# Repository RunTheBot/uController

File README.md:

# µController

µController (micro controller) a tiny battery powered game controller design for one game...unrailed

This way, you can ruin friendships with unrailed anywhere, anytime.

# Features
- Hall effect PS4 style joysticks
- 2 Cherry MX keys for use and dash inputs
- Neopixel RGB LED under Cherry MX keys
- 5v boost converter for neopixel running off 3.7v battery
- USB-C charging port
- Battery charging
- Battery voltage sensor
- Battery level indicator
- Ultra low power mode
  - Deep sleep mode with wake on button press
  - Disables boost converter and neopixel
  - Disables Wireless connection
- Ultra Small: 79mm x 33mm
- Wireless

# BOM

| Name                       | Quantity | Single Unit Price | Total Price | URL/LCSC                                                                      | Vendor (LCSC unless otheriwse indicated) |                  |
|----------------------------|----------|-------------------|-------------|-------------------------------------------------------------------------------|------------------------------------------|------------------|
| Electronics                |          |                   |             |                                                                               |                                          |                  |
| C5 0603 0.1uF              | 3        |                   | $0.45       | C49678                                                                        |                                          |                  |
| C3 0603 10uF               | 1        |                   | $0.13       | C19702                                                                        |                                          |                  |
| C4 0603 22uF               | 1        |                   | $0.18       | C59461                                                                        |                                          |                  |
| LED 0603                   | 1        |                   | $0.32       | C965799                                                                       |                                          |                  |
| SK6812MINI                 | 2        |                   | $0.37       | C5149201                                                                      |                                          |                  |
| schottky diode             | 2        |                   |             | C85098                                                                        |                                          | With NotAHackPad |
| BSS138 (Level Shifter)     | 1        |                   |             | C82045                                                                        |                                          | With NotAHackPad |
| USB_C_Receptacle           | 1        |                   | $0.38       | C2988369                                                                      |                                          |                  |
| 2.2µH/±20%/1.5A Inductor   | 1        |                   | $0.67       | C171762                                                                       |                                          |                  |
| 0603 R5.1kΩ                | 2        |                   | $0.09       | C2907044                                                                      |                                          |                  |
| 0603 1.8M                  | 1        |                   | $0.08       | C2930026                                                                      |                                          |                  |
| 0603 200k                  | 1        |                   | $0.12       | C105574                                                                       |                                          |                  |
| 0603 120Ω                  | 1        |                   | $0.13       | C114640                                                                       |                                          |                  |
| 0603 10K                   | 3        |                   |             | C98220                                                                        | With NotAHackPad                         |                  |
| 0603 15kΩ                  | 1        |                   | $0.09       | C2906995                                                                      |                                          |                  |
| 0603 100kΩ                 | 2        |                   | $0.10       | C14675                                                                        |                                          |                  |
| SW_Push_SPST_NO_Alps_SKRK  | 2        |                   | $0.63       | C115357                                                                       |                                          |                  |
| NanoS3                     | 1        |                   | $19.00      | https://unexpectedmaker.com/shop.html#!/NanoS3/p/577095557/category=154217256 | UM                                       |                  |
| TPS61200DRC                | 1        |                   | $1.63       | C140320                                                                       |                                          |                  |
| PS4 Joystick Hall Effect   | 1        |                   | $4.59       | https://www.aliexpress.com/item/1005008600410715.html                         |                                          |                  |
| BT2.0 U CablePigtail (180) | 1        |                   | $8.20       | https://www.aliexpress.com/item/1005008719531779.html                         |                                          |                  |
| Battery                    | 1        |                   | $25.79      | https://www.aliexpress.com/item/1005008702820863.html                         |                                          |                  |
| LCSC Shipping/handling     |          |                   | $15.14      |                                                                               |                                          |                  |
| UM Shipping                |          |                   | $12.95      |                                                                               |                                          |                  |
| Keys                       |          |                   |             |                                                                               |                                          |                  |
| Outemu Silent Grays        | 1        | $22.38            | $22.38      | https://www.aliexpress.com/item/1005007052759423.html                         |                                          |                  |
| Key Caps - Printed         |          |                   | $0.00       |                                                                               |                                          |                  |
| JLC                        |          |                   |             |                                                                               |                                          |                  |
| PCB with stencil           | 1        | $9.00             | $9.00       |                                                                               |                                          |                  |
| Shipping                   | 1        | $16.88            | $16.88      |                                                                               |                                          |                  |
|                            |          |                   |             |                                                                               |                                          |                  |
|                            |          |                   | $60.96      | CAD                                                                           |                                          |                  |
|                            |          |                   | $59.34      | USD                                                                           |                                          |                  |
|                            |          |                   | $103.89     | Total - USD                                                                   |                                          |                  |

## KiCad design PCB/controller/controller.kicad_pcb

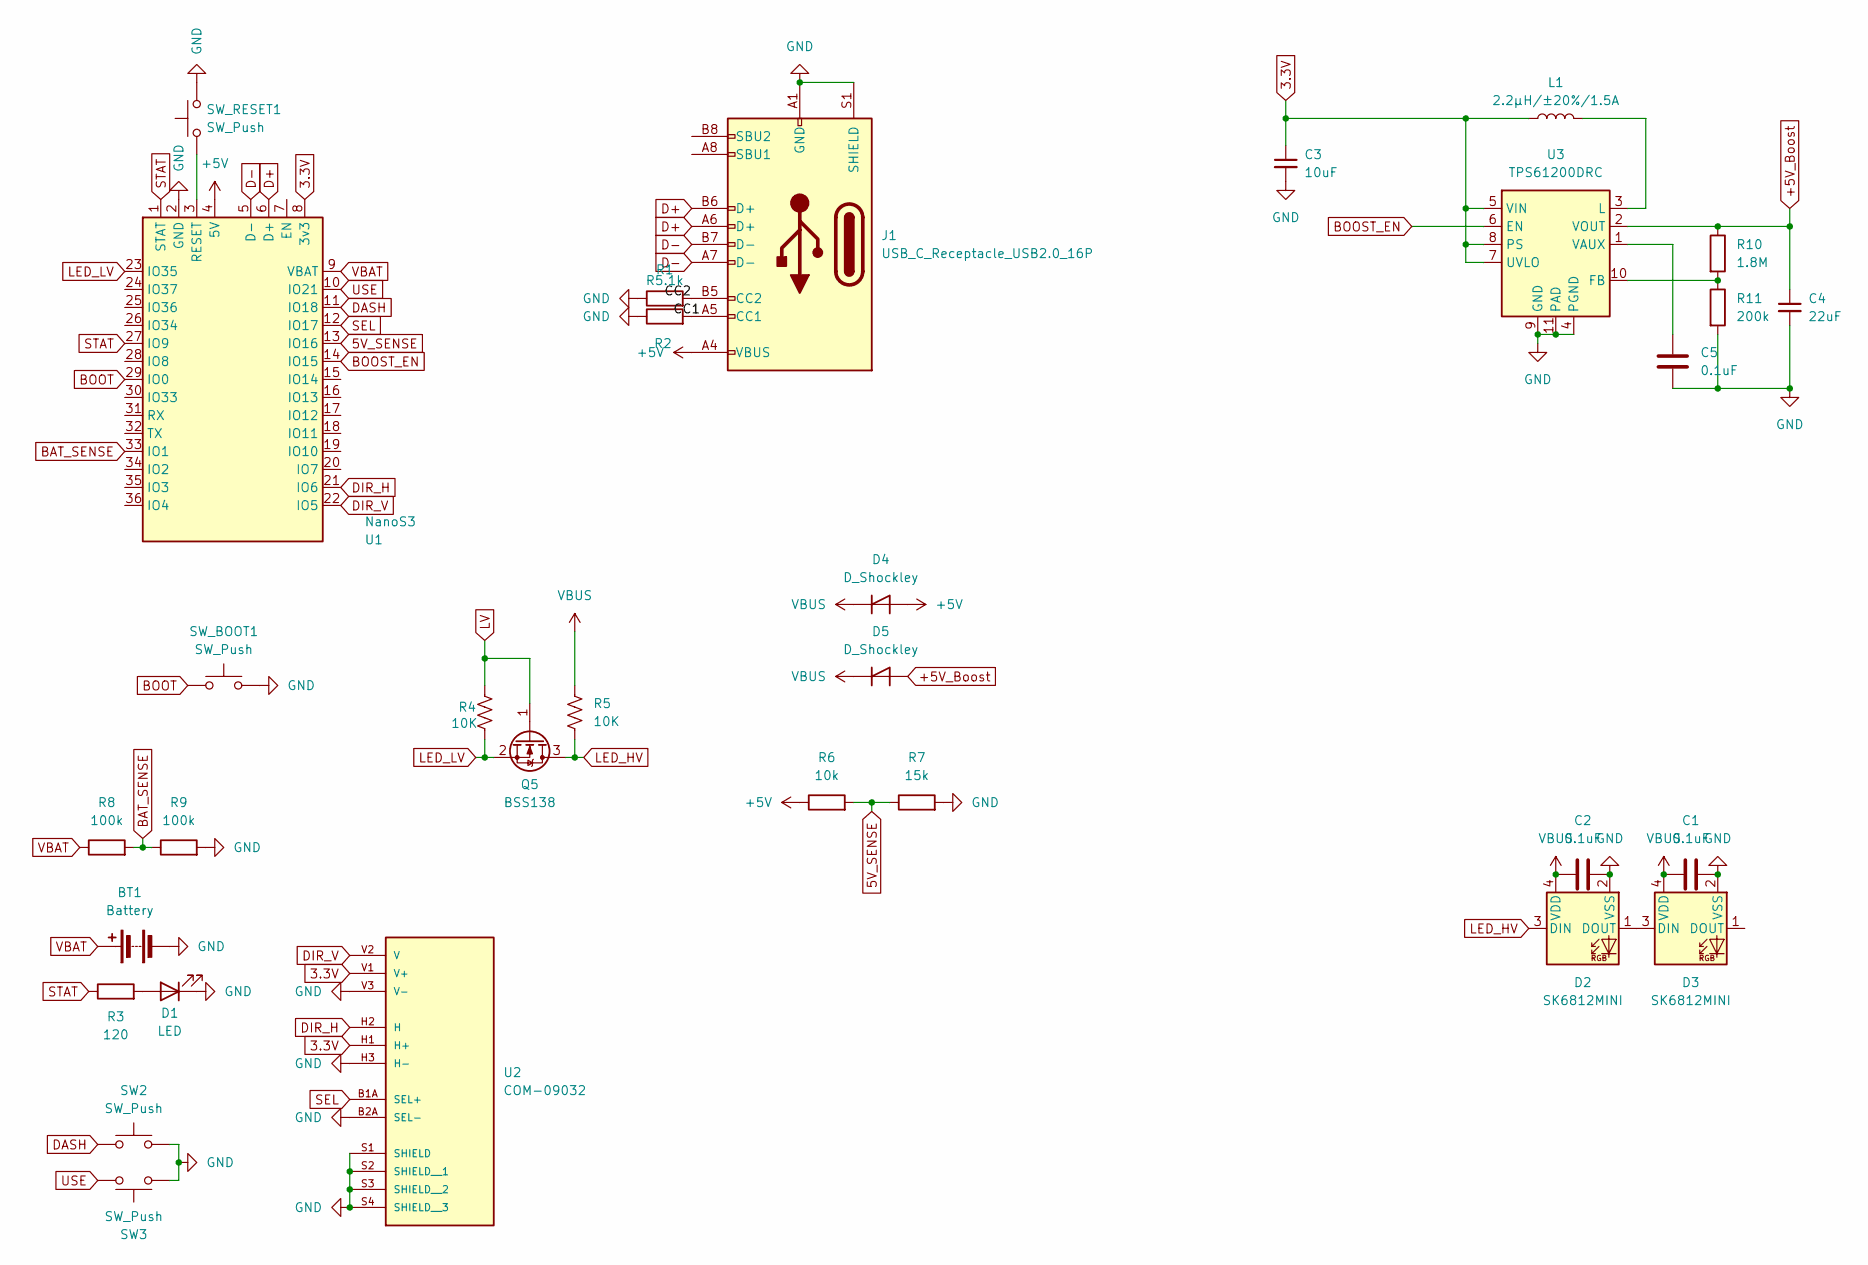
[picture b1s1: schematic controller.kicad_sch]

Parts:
BT1: Battery; JST_XH_S2B-XH-A_1x02_P2.50mm_Horizontal
C1, C2: 0.1uF; C_0805_2012Metric_Pad1.18x1.45mm_HandSolder
C3: 10uF; C_0603_1608Metric_Pad1.08x0.95mm_HandSolder
C4: 22uF; C_0603_1608Metric_Pad1.08x0.95mm_HandSolder
C5: 0.1uF; C_0603_1608Metric_Pad1.08x0.95mm_HandSolder
D1: LED; LED_0603_1608Metric_Pad1.05x0.95mm_HandSolder
D2, D3: SK6812MINI; SK6812MINI-E
D4, D5: D_Shockley; D_SMA-SMB_Universal_Handsoldering
J1: USB_C_Receptacle_USB2.0_16P; USB_C_Receptacle_G-Switch_GT-USB-7010ASV
L1: 2.2µH/±20%/1.5A; L_1008_2520Metric_Pad1.43x2.20mm_HandSolder
Q5: BSS138; SOT-23
R1, R2: R5.1k; R_0603_1608Metric_Pad0.98x0.95mm_HandSolder
R3: 120; C_0603_1608Metric_Pad1.08x0.95mm_HandSolder
R4, R5: 10K; R_0603_1608Metric_Pad0.98x0.95mm_HandSolder
R6: 10k; R_0603_1608Metric_Pad0.98x0.95mm_HandSolder
R7: 15k; R_0603_1608Metric_Pad0.98x0.95mm_HandSolder
R8, R9: 100k; R_0603_1608Metric_Pad0.98x0.95mm_HandSolder
R10: 1.8M; R_0603_1608Metric_Pad0.98x0.95mm_HandSolder
R11: 200k; R_0603_1608Metric_Pad0.98x0.95mm_HandSolder
SW2, SW3: SW_Push; SW_Cherry_MX_PCB_1.00u
SW_BOOT1: SW_Push; SW_Push_SPST_NO_Alps_SKRK
SW_RESET1: SW_Push; SW_Push_SPST_NO_Alps_SKRK
U1: NanoS3; NanoS3_HandSolder
U2: COM-09032; PS4_joystick; PARTREV N/A
U3: TPS61200DRC; Texas_S-PVSON-N10_ThermalVias

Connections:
3.3V: C3.1, L1.1, U1.8 (3v3), U2.H1 (H+), U2.V1 (V+), U3.5 (VIN), U3.7 (UVLO), U3.8 (PS)
5V_SENSE: R6.2, R7.1, U1.13 (IO16)
+5V: D4.2 (A), J1.A4 (VBUS), J1.A9 (VBUS), J1.B4 (VBUS), J1.B9 (VBUS), R6.1, U1.4 (5V)
+5V_Boost: C4.1, D5.2 (A), R10.1, U3.2 (VOUT)
/CC2: J1.B5 (CC2), R1.2
BAT_SENSE: R8.2, R9.1, U1.33 (IO1)
BOOST_EN: U1.14 (IO15), U3.6 (EN)
BOOT: SW_BOOT1.1, U1.29 (IO0)
D+: J1.A6 (D+), J1.B6 (D+), U1.6 (D+)
D-: J1.A7 (D-), J1.B7 (D-), U1.5 (D-)
DASH: SW2.1, U1.11 (IO18)
DIR_H: U1.21 (IO6), U2.H2 (H)
DIR_V: U1.22 (IO5), U2.V2 (V)
GND: BT1.2 (-), C1.2, C2.2, C3.2, C4.2, C5.1, D1.1 (K), D2.2 (VSS), D3.2 (VSS), J1.A1 (GND), J1.A12 (GND), J1.B1 (GND), J1.B12 (GND), J1.S1 (SHIELD), R1.1, R2.1, R7.2, R9.2, R11.2, SW2.2, SW3.1, SW_BOOT1.2, SW_RESET1.2, U1.2 (GND), U2.B2A (SEL-), U2.H3 (H-), U2.S1 (SHIELD), U2.S2 (SHIELD__1), U2.S3 (SHIELD__2), U2.S4 (SHIELD__3), U2.V3 (V-), U3.4 (PGND), U3.9 (GND), U3.11 (PAD)
LED_HV: D2.3 (DIN), Q5.3 (D), R5.2
LED_LV: Q5.2 (S), R4.2, U1.23 (IO35)
LV: Q5.1 (G), R4.1
unnamed: D1.2 (A), R3.2
unnamed: D2.1 (DOUT), D3.3 (DIN)
unnamed: J1.A5 (CC1), R2.2
unnamed: SW_RESET1.1, U1.3 (RESET)
unnamed: R10.2, R11.1, U3.10 (FB)
unnamed: L1.2, U3.3 (L)
unnamed: C5.2, U3.1 (VAUX)
SEL: U1.12 (IO17), U2.B1A (SEL+)
STAT: R3.1, U1.1 (STAT), U1.27 (IO9)
USE: SW3.2, U1.10 (IO21)
VBAT: BT1.1 (+), R8.1, U1.9 (VBAT)
VBUS: C1.1, C2.1, D2.4 (VDD), D3.4 (VDD), D4.1 (K), D5.1 (K), R5.1

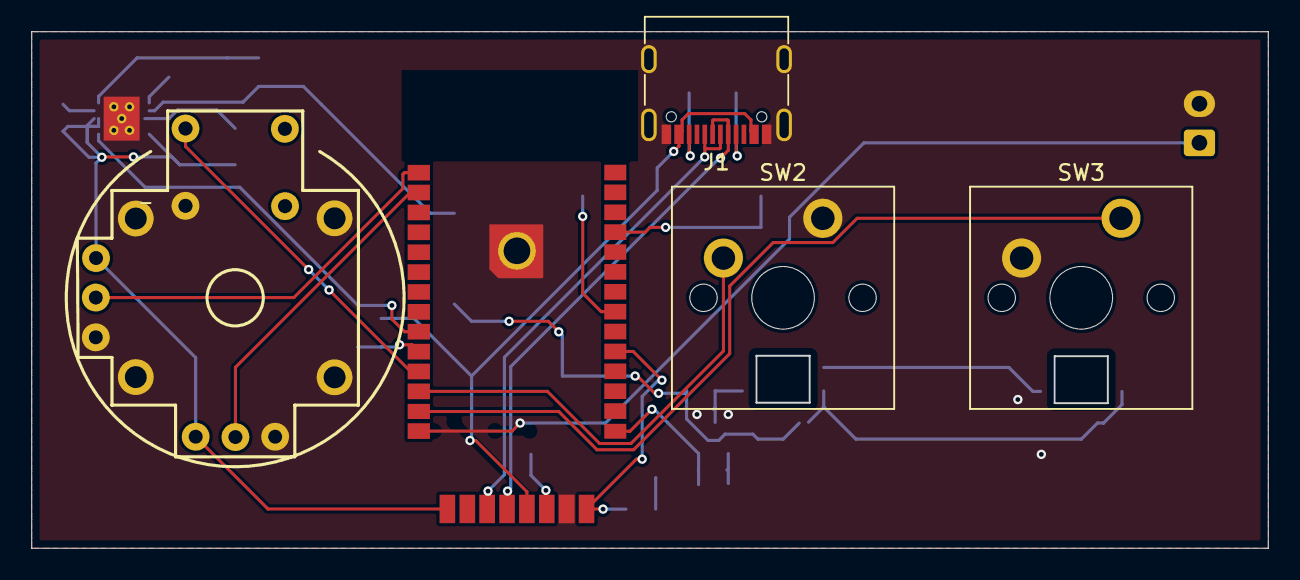
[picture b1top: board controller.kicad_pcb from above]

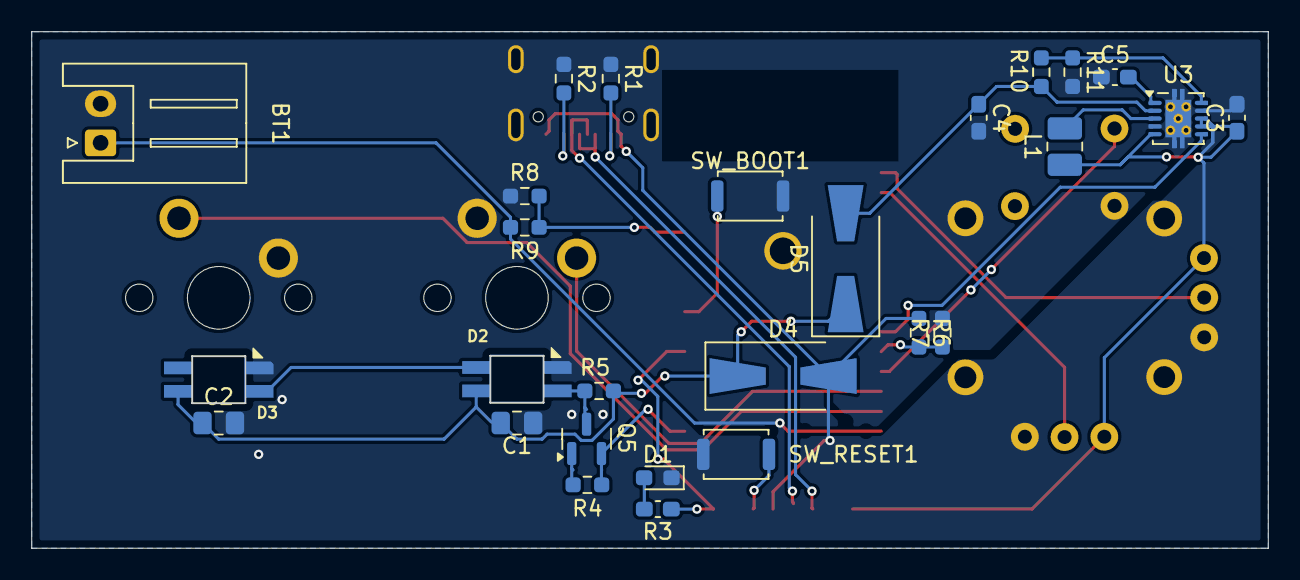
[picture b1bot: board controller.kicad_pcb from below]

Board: 2 copper layers, 78.9 x 32.9 mm, 32 parts (27 on the bottom side), 29 nets.

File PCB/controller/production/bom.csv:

Designator,Footprint,Quantity,Value,LCSC Part #
BT1,JST_XH_S2B-XH-A_1x02_P2.50mm_Horizontal,1,Battery,C493111
"C1, C2, C5",0805,3,0.1uF,C49678
C3,0603,1,10uF,C19702
C4,0603,1,22uF,C59461
D1,0603,1,LED,C965799
"D2, D3",SK6812MINI-E,2,SK6812MINI,C5149201
"D4, D5",D_SMA-SMB_Universal_Handsoldering,2,D_Shockley,C85098
J1,USB_C_Receptacle_XKB_U262-16XN-4BVC11,1,USB_C_Receptacle_USB2.0_16P,
L1,1008,1,2.2µH/±20%/1.5A,C2988369
Q5,SOT-23,1,BSS138,C171762
"R1, R2",0603,2,R5.1k,C2907044
R10,0603,1,1.8M,C2930026
R11,0603,1,200k,C105574
R3,0603,1,120,C114640
"R4, R5, R6",0603,3,10K,C98220
R7,0603,1,15k,C2906995
"R8, R9",0603,2,100k,C14675
"SW2, SW3",SW_Cherry_MX_PCB_1.00u,2,SW_Push,
"SW_BOOT1, SW_RESET1",SW_Push_SPST_NO_Alps_SKRK,2,SW_Push,C115357
U1,NanoS3_HandSolder,1,NanoS3,
U2,PS4_joystick,1,COM-09032,
U3,Texas_S-PVSON-N10_ThermalVias,1,TPS61200DRC,C140320

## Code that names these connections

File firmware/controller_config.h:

/*
 * ESP32-S3 Unrailed Controller Configuration
 * Hardware: NanoS3/Tiny Pico Nano
 */

#ifndef CONTROLLER_CONFIG_H
#define CONTROLLER_CONFIG_H

// Hardware version
#define HARDWARE_VERSION "NanoS3/Tiny Pico Nano"
#define FIRMWARE_VERSION "1.0.0"

// Pin definitions for ESP32-S3
#define LED_LV_PIN      35  // Status LED
#define BAT_STAT_PIN    9   // Battery Status Input
#define BAT_SENSE_PIN   1   // Battery Voltage ADC (100k/100k divider)
#define USE_PIN         21  // Button A (USE)
#define DASH_PIN        18  // Button B (DASH)
#define SEL_PIN         17  // Select Button
#define USB_5V_SENSE    16  // USB 5V Detection
#define BOOST_EN_PIN    15  // 5V Boost Enable
#define DIR_H_PIN       6   // Joystick Horizontal (X-axis)
#define DIR_V_PIN       5   // Joystick Vertical (Y-axis)

// Controller settings
#define CONTROLLER_NAME "Unrailed Controller"
#define MANUFACTURER    "ESP32"

// Joystick configuration
#define JOYSTICK_DEADZONE     100   // ADC units
#define JOYSTICK_CENTER       2048  // 12-bit ADC center
#define JOYSTICK_MAX_RANGE    2048  // Maximum deviation from center

// Battery configuration
#define BATTERY_CHECK_INTERVAL 5000  // milliseconds
#define BATTERY_MIN_VOLTAGE    3.0   // Volts
#define BATTERY_MAX_VOLTAGE    4.2   // Volts (fully charged Li-Po)
#define VOLTAGE_DIVIDER_RATIO  2.0   // 100k/100k = 2:1 ratio

// LED patterns
#define LED_BLINK_INTERVAL    500   // milliseconds (when not connected)
#define LED_STARTUP_BLINKS    3     // Number of blinks on startup

// Deep sleep configuration
#define SLEEP_TIMEOUT_MS         300000  // 5 minutes of inactivity before sleep
#define LOW_BATTERY_SLEEP_MS     30000   // 30 seconds between wake cycles when low battery
#define ACTIVITY_THRESHOLD       50      // Joystick movement threshold to detect activity
#define LOW_BATTERY_THRESHOLD    15      // Battery percentage threshold for extended sleep

// Wake up sources - Require ALL 3 buttons pressed simultaneously
#define WAKE_BUTTON_BITMASK      0x2A0000  // USE (GPIO21), DASH (GPIO18), and SEL (GPIO17) buttons
// Bitmask calculation: (1ULL << USE_PIN) | (1ULL << DASH_PIN) | (1ULL << SEL_PIN) 
// = (1ULL << 21) | (1ULL << 18) | (1ULL << 17) = 0x2A0000

// Button mapping for Unrailed game
typedef enum {
    GAMEPAD_BUTTON_A = 1,      // USE button -> A
    GAMEPAD_BUTTON_B = 2,      // DASH button -> B
    GAMEPAD_BUTTON_SELECT = 8  // SEL button -> Select
} GamepadButtons;

// Joystick mapping
typedef enum {
    JOYSTICK_LEFT_X = 0,   // DIR_H -> Left stick X
    JOYSTICK_LEFT_Y = 1    // DIR_V -> Left stick Y (inverted)
} JoystickAxes;

#endif // CONTROLLER_CONFIG_H

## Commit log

2025-06-07 init
2025-06-07 sadasd
2025-06-07 Add lock files for PCB controller and schematic with user information
2025-06-08 Refactor code structure for improved readability and maintainability
2025-06-08 Add autosave lock file for controller with hostname and username
2025-06-08 Update hours logged for 06/04/2025 from 3h to 9h
2025-06-08 Add metadata section to journal.md for project details
2025-06-09 Add production files for PCB controller design
    - Created designators.csv with component designators and their counts.
    - Added netlist.ipc containing detailed netlist information for PCB connections.
    - Introduced positions.csv to specify component positions, rotations, and layers on the PCB.
2025-06-09 Add BOM file for µController with component details and pricing
2025-06-09 Add additional image to README.md for enhanced visual representation
2025-06-09 Add lock file for PCB controller with hostname and username information
2025-06-09 Firmware
